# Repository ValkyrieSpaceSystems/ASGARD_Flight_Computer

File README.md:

# Asgard Flight Computer

An open-source high power rocketry flight computer designed for long-term affordability through flexibility, modularity, and expandability. Designed to fly with [ODIN flight software](https://github.com/ValkyrieSpaceSystems/ODIN_Flight_Software) and communicate with the [Midgard ground station](https://github.com/ValkyrieSpaceSystems/MIDGARD_Ground_Control) over the [BIFROST protocol](https://github.com/ValkyrieSpaceSystems/BIFROST_Communications_Protocol).

---

## Sensors

| Component | Part | Interface |
|---|---|---|
| Low-altitude barometer | BMP581 | SPI |
| High-altitude barometer *(optional)* | MS5607 | SPI |
| Low-g IMU | BMI270 | SPI |
| Mid-g IMU | BMI088 | SPI |
| High-g accelerometer | H3LIS331DLTR | SPI |
| Magnetometer | MMC5983MA | SPI |
| GNSS | MAX-M10S | UART |
| Current monitor | INA226 | I2C |

---

## Pyrotechnics

3 independent events, 2 channels each (6 total). High-side arming via external switch keeps all channels unpowered until deliberately armed. Each channel has its own independent low-side MOSFET.

---

## Servo Control

6 outputs — a 4-channel group for fin deflection and a 2-channel group for thrust vector control. Each group is independently configurable via jumper to run from battery or regulated 5V.

---

## Communications

Interface agnostic — any physical transport (XBee, ELRS, RS-485, Bluetooth, CAN, USB, etc.) can carry BIFROST traffic with no firmware changes. A bypass switch port enables autonomous operation if ground station comms are unavailable.

---

## Expansion

2× SPI, 3× UART, 2× I2C, 1× CAN expansion ports, plus 2 GPIO breakout pins. Pyro arm and servo arm signals are also broken out for auxiliary boards.

**Current expansion boards:** RS-485, GPIO breakout

**Planned:** camera module, extra sensors, payload, multi-stage, Bluetooth/WiFi, high-power servos, pyro expansion

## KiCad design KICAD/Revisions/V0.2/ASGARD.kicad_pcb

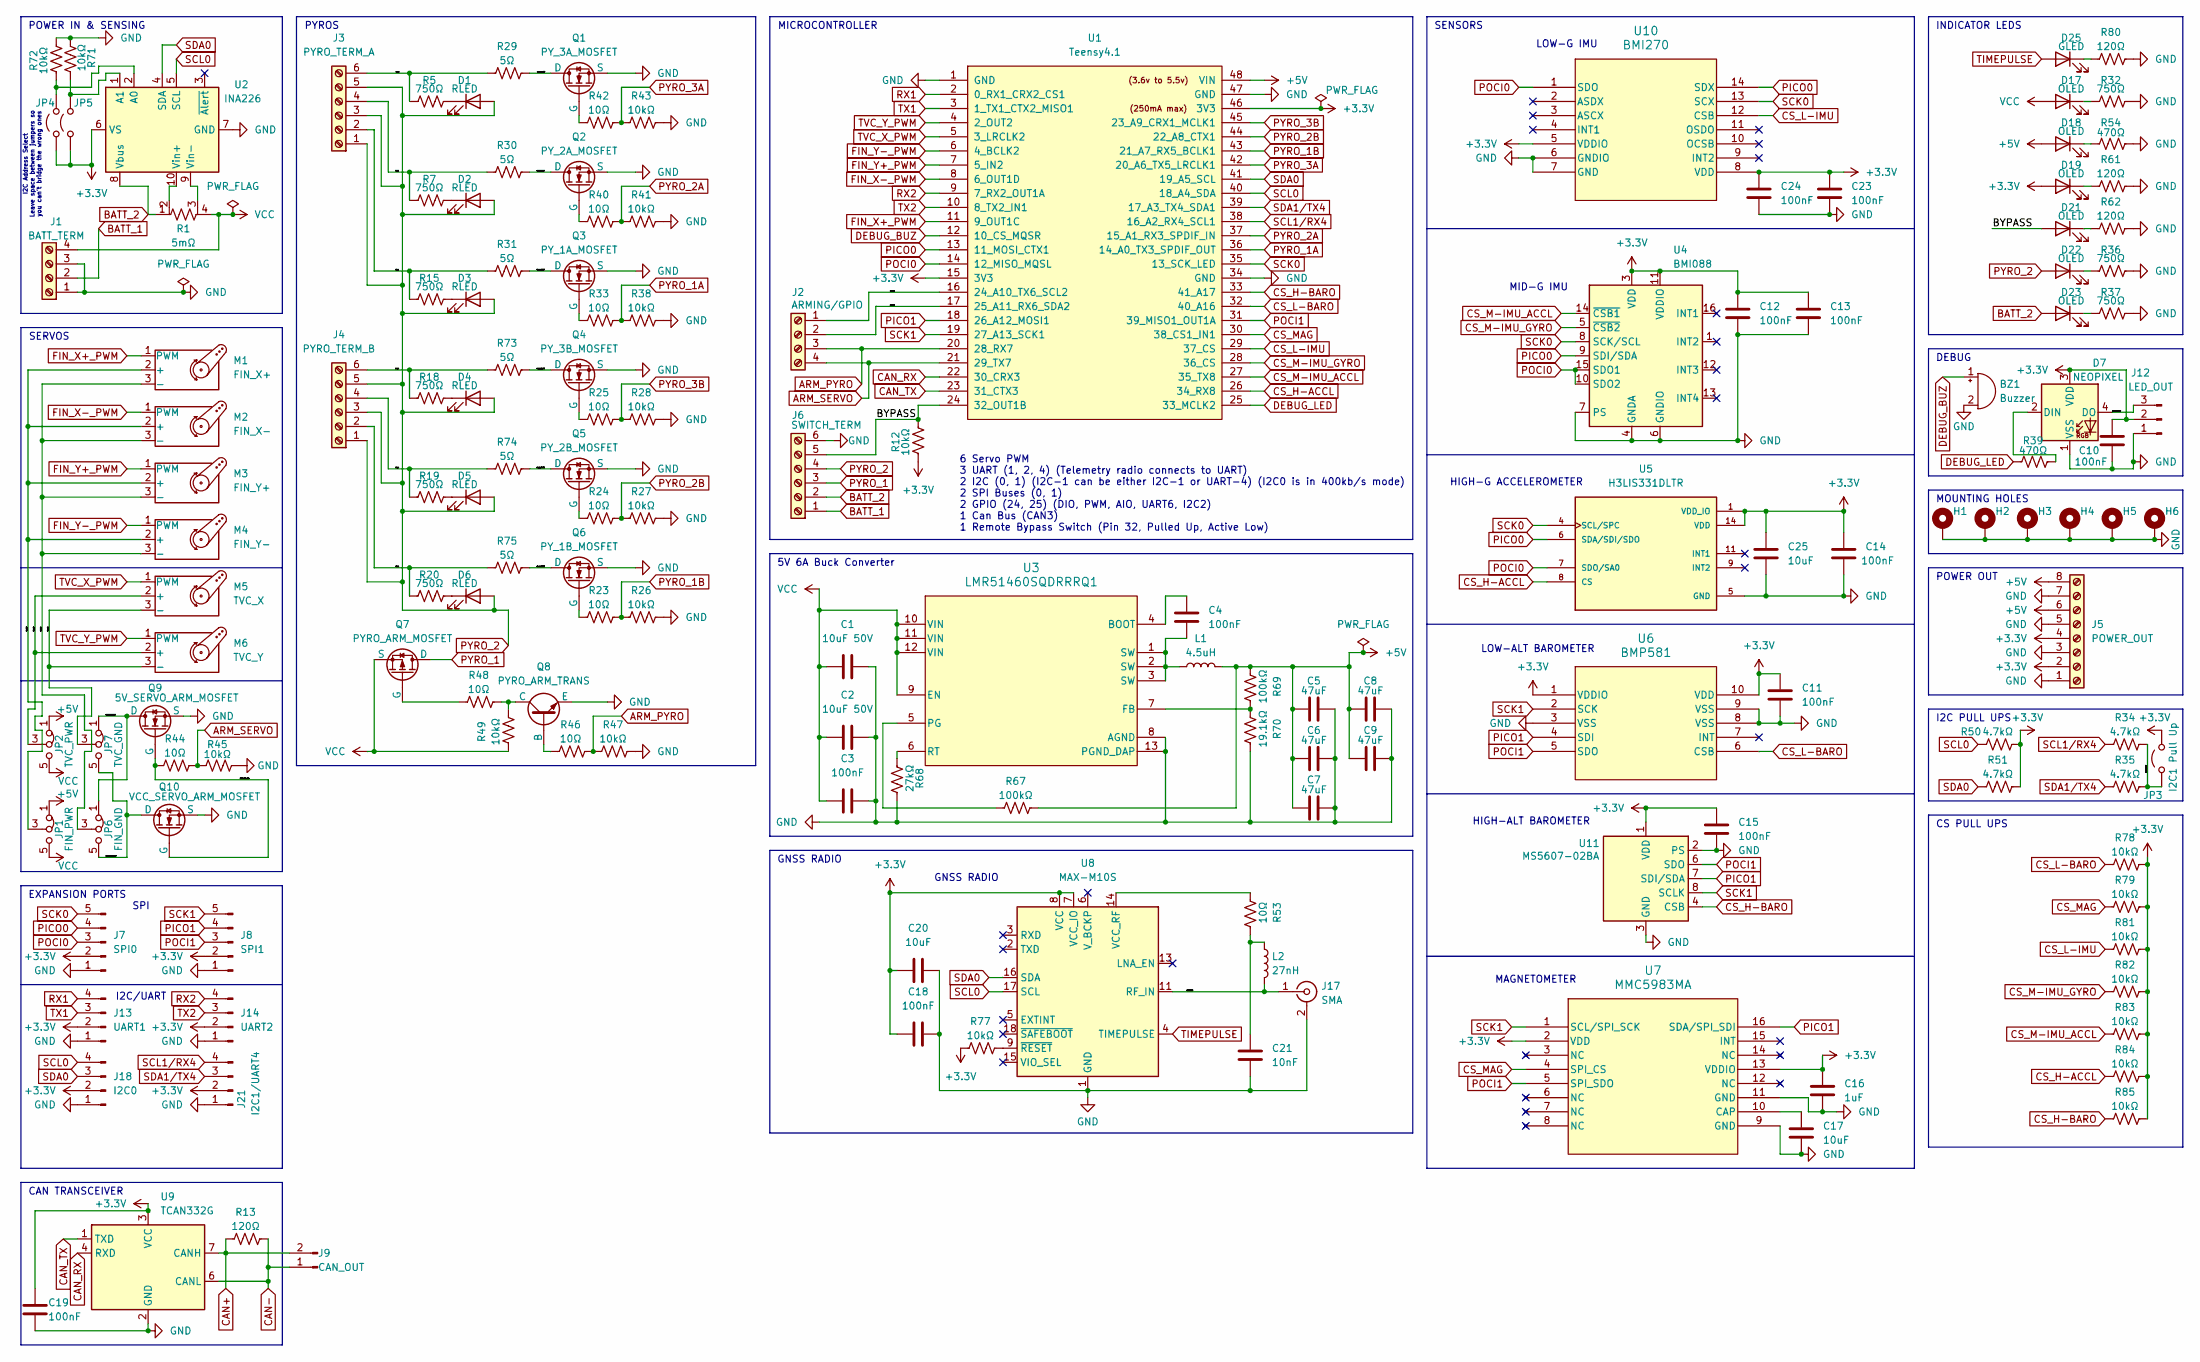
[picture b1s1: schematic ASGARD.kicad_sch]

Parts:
BZ1: Buzzer; Buzzer_CUI_CPT-9019S-SMT
C1, C2: 10uF 50V; C_1210_3225Metric
C3, C4, C10, C11, C12, C13, C14, C15, C18, C19, C23, C24: 100nF; C_0603_1608Metric
C5, C6, C7, C8, C9: 47uF; C_1210_3225Metric
C16: 1uF; C_0603_1608Metric
C17, C20, C25: 10uF; C_0603_1608Metric
C21: 10nF; C_0603_1608Metric
D1, D2, D3, D4, D5, D6: RLED; LED_0603_1608Metric
D7: NEOPIXEL; LED_Inolux_IN-PI554FCH_PLCC4_5.0x5.0mm_P3.2mm
D17, D18, D19, D21, D22, D23: OLED; LED_0603_1608Metric
D25: GLED; LED_0603_1608Metric
H1, H2, H3, H4, H5, H6: MountingHole_Pad; MountingHole_2.5mm_Pad
J1: BATT_TERM; TerminalBlock_4Ucon_1x04_P3.50mm_Horizontal
J2: ARMING/GPIO; TerminalBlock_4Ucon_1x04_P3.50mm_Horizontal
J3: PYRO_TERM_A; TerminalBlock_4Ucon_1x06_P3.50mm_Horizontal
J4: PYRO_TERM_B; TerminalBlock_4Ucon_1x06_P3.50mm_Horizontal
J5: POWER_OUT; TerminalBlock_4Ucon_1x08_P3.50mm_Horizontal
J6: SWITCH_TERM; TerminalBlock_4Ucon_1x06_P3.50mm_Horizontal
J7: SPI0; JST_SH_BM05B-SRSS-TB_1x05-1MP_P1.00mm_Vertical
J8: SPI1; JST_SH_BM05B-SRSS-TB_1x05-1MP_P1.00mm_Vertical
J9: CAN_OUT; JST_SH_BM02B-SRSS-TB_1x02-1MP_P1.00mm_Vertical
J12: LED_OUT; JST_SH_BM03B-SRSS-TB_1x03-1MP_P1.00mm_Vertical
J13: UART1; JST_SH_BM04B-SRSS-TB_1x04-1MP_P1.00mm_Vertical
J14: UART2; JST_SH_BM04B-SRSS-TB_1x04-1MP_P1.00mm_Vertical
J17: SMA; SMA_Amphenol_132134-11_Vertical
J18: I2C0; JST_SH_BM04B-SRSS-TB_1x04-1MP_P1.00mm_Vertical
J21: I2C1/UART4; JST_SH_BM04B-SRSS-TB_1x04-1MP_P1.00mm_Vertical
JP1: FIN_PWR; PinHeader_2x03_P2.54mm_Vertical
JP2: TVC_PWR; PinHeader_2x03_P2.54mm_Vertical
JP3: I2C1 Pull Up; PinHeader_1x02_P2.54mm_Vertical
JP4, JP5: Jumper_2_Open; PinHeader_1x02_P2.54mm_Vertical
JP6: FIN_GND; PinHeader_2x03_P2.54mm_Vertical
JP7: TVC_GND; PinHeader_2x03_P2.54mm_Vertical
L1: 4.5uH; IND_SRR1208-120ML
L2: 27nH; L_0402_1005Metric
M1: FIN_X+; PinHeader_1x03_P2.54mm_Vertical
M2: FIN_X-; PinHeader_1x03_P2.54mm_Vertical
M3: FIN_Y+; PinHeader_1x03_P2.54mm_Vertical
M4: FIN_Y-; PinHeader_1x03_P2.54mm_Vertical
M5: TVC_X; PinHeader_1x03_P2.54mm_Vertical
M6: TVC_Y; PinHeader_1x03_P2.54mm_Vertical
Q1: PY_3A_MOSFET; SOT-23-3
Q2: PY_2A_MOSFET; SOT-23-3
Q3: PY_1A_MOSFET; SOT-23-3
Q4: PY_3B_MOSFET; SOT-23-3
Q5: PY_2B_MOSFET; SOT-23-3
Q6: PY_1B_MOSFET; SOT-23-3
Q7: PYRO_ARM_MOSFET; SOT-23-6_Handsoldering
Q8: PYRO_ARM_TRANS; SOT-23-3
Q9: 5V_SERVO_ARM_MOSFET; Infineon_PG-TDSON-8_6.15x5.15mm
Q10: VCC_SERVO_ARM_MOSFET; Infineon_PG-TDSON-8_6.15x5.15mm
R1: 5mΩ; RES_WSLP2726L2000FEA
R5, R7, R15, R18, R19, R20, R32, R36, R37: 750Ω; R_0805_2012Metric
R12, R26, R27, R28, R38, R41, R43, R45, R47, R49, R71, R72, R77, R78, R79, R81, R82, R83, R84, R85: 10kΩ; R_0805_2012Metric
R13, R61, R62, R80: 120Ω; R_0805_2012Metric
R23, R24, R25, R33, R40, R42, R44, R46, R48, R53: 10Ω; R_0805_2012Metric
R29, R30, R31, R73, R74, R75: 5Ω; R_0805_2012Metric
R34, R35, R50, R51: 4.7kΩ; R_0805_2012Metric
R39, R54: 470Ω; R_0805_2012Metric
R67, R69: 100kΩ; R_0805_2012Metric
R68: 27kΩ; R_0805_2012Metric
R70: 19.1kΩ; R_0805_2012Metric
U1: Teensy4.1; Teensy41
U2: INA226; TSSOP-10_3x3mm_P0.5mm
U3: LMR51460SQDRRRQ1; DRR0012E-IPC_A
U4: BMI088; Bosch_LGA-16_4.5x3mm_P0.5mm_LayoutBorder7x1y_ClockwisePinNu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
U5: H3LIS331DLTR; QFN300X300X100-16N
U6: BMP581; QFN10_BMP581_BOS
U7: MMC5983MA; MMC5983MA_MEM
U8: MAX-M10S; ublox_MAX
U9: TCAN332G; TSOT-23-8_HandSoldering
U10: BMI270; BMI270_BOS
U11: MS5607-02BA; LGA-8_3x5mm_P1.25mm

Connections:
+3.3V: C10.2, C11.2, C12.1, C13.2, C14.2, C15.2, C16.1, C18.2, C19.1, C20.1, C23.1, C24.2, C25.1, D7.3 (VDD), D19.2 (A), J5.2, J5.4, J7.2, J8.2, J12.2, J13.2, J14.2, J18.2, J21.2, JP3.2 (B), JP4.1 (A), JP5.1 (A), R12.1, R50.2, R51.2, R77.1, R78.2, R79.2, R81.2, R82.2, R83.2, R84.2, R85.2, U1.15 (3V3), U1.46 (3V3), U2.6 (VS), U4.3 (VDD), U4.11 (VDDIO), U5.1 (VDD_IO), U5.14 (VDD), U5.15 (VDD), U6.1 (VDDIO), U6.10 (VDD), U7.2 (VDD), U7.13 (VDDIO), U8.7 (VCC_IO), U8.8 (VCC), U9.3 (VCC), U10.5 (VDDIO), U10.8 (VDD), U11.1 (VDD)
+5V: C5.2, C6.2, C7.2, C8.2, C9.2, D18.2 (A), J5.6, J5.8, JP1.1 (A), JP2.1 (A), L1.2, R67.2, R69.1, U1.48 (VIN)
/5V_SERVO_MOSFET: JP6.1 (A), JP7.1 (A), Q9.5 (D)
/BYPASS: D21.2 (A), J6.5, R12.2, U1.24 (32_OUT1B)
/DEBUG_LED_OUT: D7.4 (DO), J12.3
/FIN_GND: JP6.3 (C), M1.3 (-), M2.3 (-), M3.3 (-), M4.3 (-)
/FIN_PWR: JP1.3 (C), M1.2 (+), M2.2 (+), M3.2 (+), M4.2 (+)
/GPIO_24: J2.1, U1.16 (24_A10_TX6_SCL2)
/GPIO_25: J2.2, U1.17 (25_A11_RX6_SDA2)
/I2C1_PULL_UP: JP3.1 (A), R34.2, R35.2
/MICROSTRIP: J17.1 (In), L2.2, U8.11 (RF_IN)
/PY_1A: J3.2, R15.1, R31.1
/PY_1A_MOSFET: Q3.3 (D), R31.2
/PY_1B: J4.2, R20.1, R75.1
/PY_1B_MOSFET: Q6.3 (D), R75.2
/PY_2A: J3.4, R7.1, R30.1
/PY_2A_MOSFET: Q2.3 (D), R30.2
/PY_2B: J4.4, R19.1, R74.1
/PY_2B_MOSFET: Q5.3 (D), R74.2
/PY_3A: J3.6, R5.1, R29.1
/PY_3A_MOSFET: Q1.3 (D), R29.2
/PY_3B: J4.6, R18.1, R73.1
/PY_3B_MOSFET: Q4.3 (D), R73.2
/SERVO_ARM_GATE: Q9.4 (G), Q10.4 (G), R44.1
/TVC_GND: JP7.3 (C), M5.3 (-), M6.3 (-)
/TVC_PWR: JP2.3 (C), M5.2 (+), M6.2 (+)
/VCC_SERVO_MOSFET: JP6.5 (B), JP7.5 (B), Q10.5 (D)
ARM_PYRO: J2.3, R46.2, R47.1, U1.20 (28_RX7)
ARM_SERVO: J2.4, R44.2, R45.1, U1.21 (29_TX7)
BATT_1: J1.2, J6.1
BATT_2: D23.2 (A), J6.2, R1.1, U2.8 (Vbus)
CAN+: J9.2, R13.1, U9.7 (CANH)
CAN-: J9.1, R13.2, U9.6 (CANL)
CAN_RX: U1.22 (30_CRX3), U9.4 (RXD)
CAN_TX: U1.23 (31_CTX3), U9.1 (TXD)
CS_H-ACCL: R84.1, U1.26 (34_RX8), U5.8 (CS)
CS_H-BARO: R85.1, U1.33 (41_A17), U11.4 (CSB), U11.5 (CSB)
CS_L-BARO: R78.1, U1.32 (40_A16), U6.6 (CSB)
CS_L-IMU: R81.1, U1.29 (37_CS), U10.12 (CSB)
CS_M-IMU_ACCL: R83.1, U1.27 (35_TX8), U4.14 (~CSB1)
CS_M-IMU_GYRO: R82.1, U1.28 (36_CS), U4.5 (~CSB2)
CS_MAG: R79.1, U1.30 (38_CS1_IN1), U7.4 (SPI_CS)
DEBUG_BUZ: BZ1.1 (+), U1.12 (10_CS_MQSR)
DEBUG_LED: R39.1, U1.25 (33_MCLK2)
FIN_X+_PWM: M1.1 (PWM), U1.11 (9_OUT1C)
FIN_X-_PWM: M2.1 (PWM), U1.8 (6_OUT1D)
FIN_Y+_PWM: M3.1 (PWM), U1.7 (5_IN2)
FIN_Y-_PWM: M4.1 (PWM), U1.6 (4_BCLK2)
GND: BZ1.2 (-), C1.2, C2.2, C3.2, C5.1, C6.1, C7.1, C8.1, C9.1, C10.1, C11.1, C12.2, C13.1, C14.1, C15.1, C16.2, C17.2, C18.1, C19.2, C20.2, C21.2, C23.2, C24.1, C25.2, D7.1 (VSS), H1.1 (1_1), H2.1 (1_1), H3.1 (1_1), H4.1 (1_1), H5.1 (1_1), H6.1 (1_1), J1.1, J1.3, J5.1, J5.3, J5.5, J5.7, J6.6, J7.1, J8.1, J12.1, J13.1, J14.1, J17.2 (Ext), J18.1, J21.1, Q1.2 (S), Q2.2 (S), Q3.2 (S), Q4.2 (S), Q5.2 (S), Q6.2 (S), Q8.2 (E), Q9.1 (S), Q10.1 (S), R26.2, R27.2, R28.2, R32.2, R36.2, R37.2, R38.2, R41.2, R43.2, R45.2, R47.2, R54.2, R61.2, R62.2, R68.2, R70.2, R71.1, R72.2, R80.2, U1.1 (GND), U1.34 (GND), U1.47 (GND), U2.7 (GND), U3.8 (AGND), U3.13 (PGND_DAP), U4.2 (GNDA), U4.4 (GNDA), U4.6 (GNDIO), U4.7 (PS), U5.5 (GND), U5.10 (GND), U5.12 (GND), U5.13 (GND), U5.16 (GND), U6.3 (VSS), U6.8 (VSS), U6.9 (VSS), U7.9 (GND), U7.11 (GND), U8.1 (GND), U8.10 (GND), U8.12 (GND), U9.2 (GND), U10.6 (GNDIO), U10.7 (GND), U11.2 (PS), U11.3 (GND)
unnamed: C4.2, L1.1, U3.1 (SW), U3.2 (SW), U3.3 (SW)
unnamed: C21.1, L2.1, R53.2
unnamed: D1.1 (K), R5.2
unnamed: D2.1 (K), R7.2
unnamed: D3.1 (K), R15.2
unnamed: D4.1 (K), R18.2
unnamed: D5.1 (K), R19.2
unnamed: D6.1 (K), R20.2
unnamed: D7.2 (DIN), R39.2
unnamed: D17.1 (K), R32.1
unnamed: D18.1 (K), R54.1
unnamed: D19.1 (K), R61.1
unnamed: D21.1 (K), R62.1
unnamed: D22.1 (K), R36.1
unnamed: D23.1 (K), R37.1
unnamed: D25.1 (K), R80.1
unnamed: JP4.2 (B), R72.1, U2.2 (A0)
unnamed: JP5.2 (B), R71.2, U2.1 (A1)
unnamed: Q1.1 (G), R42.1
unnamed: Q2.1 (G), R40.1
unnamed: Q3.1 (G), R33.1
unnamed: Q4.1 (G), R25.1
unnamed: Q5.1 (G), R24.1
unnamed: Q6.1 (G), R23.1
unnamed: Q7.3 (G), R48.1
unnamed: Q8.1 (B), R46.1
unnamed: Q8.3 (C), R48.2, R49.2
unnamed: R1.2, U2.10 (Vin+)
unnamed: R1.3, U2.9 (Vin-)
unnamed: C4.1, U3.4 (BOOT)
unnamed: R69.2, R70.1, U3.7 (FB)
unnamed: R67.1, U3.5 (PG)
unnamed: R68.1, U3.6 (RT)
unnamed: C17.1, U7.10 (CAP)
unnamed: R53.1, U8.14 (VCC_RF)
unnamed: R77.2, U8.9 (~RESET)
PICO0: J7.4, U1.13 (11_MOSI_CTX1), U4.9 (SDI/SDA), U5.6 (SDA/SDI/SDO), U10.14 (SDX)
PICO1: J8.4, U1.18 (26_A12_MOSI1), U6.4 (SDI), U7.16 (SDA/SPI_SDI), U11.7 (SDI/SDA)
POCI0: J7.3, U1.14 (12_MISO_MQSL), U4.10 (SDO2), U4.15 (SDO1), U5.7 (SDO/SA0), U10.1 (SDO)
POCI1: J8.3, U1.31 (39_MISO1_OUT1A), U6.5 (SDO), U7.5 (SPI_SDO), U11.6 (SDO)
PYRO_1: J6.3, Q7.1 (D)
PYRO_1A: R33.2, R38.1, U1.36 (14_A0_TX3_SPDIF_OUT)
PYRO_1B: R23.2, R26.1, U1.43 (21_A7_RX5_BCLK1)
PYRO_2: D1.2 (A), D2.2 (A), D3.2 (A), D4.2 (A), D5.2 (A), D6.2 (A), D22.2 (A), J3.1, J3.3, J3.5, J4.1, J4.3, J4.5, J6.4
PYRO_2A: R40.2, R41.1, U1.37 (15_A1_RX3_SPDIF_IN)
PYRO_2B: R24.2, R27.1, U1.44 (22_A8_CTX1)
PYRO_3A: R42.2, R43.1, U1.42 (20_A6_TX5_LRCLK1)
PYRO_3B: R25.2, R28.1, U1.45 (23_A9_CRX1_MCLK1)
RX1: J13.4, U1.2 (0_RX1_CRX2_CS1)
RX2: J14.4, U1.9 (7_RX2_OUT1A)
SCK0: J7.5, U1.35 (13_SCK_LED), U4.8 (SCK/SCL), U5.4 (SCL/SPC), U10.13 (SCX)
SCK1: J8.5, U1.19 (27_A13_SCK1), U6.2 (SCK), U7.1 (SCL/SPI_SCK), U11.8 (SCLK)
SCL0: J18.4, R50.1, U1.40 (18_A4_SDA), U2.5 (SCL), U8.17 (SCL)
SCL1/RX4: J21.4, R34.1, U1.38 (16_A2_RX4_SCL1)
SDA0: J18.3, R51.1, U1.41 (19_A5_SCL), U2.4 (SDA), U8.16 (SDA)
SDA1/TX4: J21.3, R35.1, U1.39 (17_A3_TX4_SDA1)
TIMEPULSE: D25.2 (A), U8.4 (TIMEPULSE)
TVC_X_PWM: M5.1 (PWM), U1.5 (3_LRCLK2)
TVC_Y_PWM: M6.1 (PWM), U1.4 (2_OUT2)
TX1: J13.3, U1.3 (1_TX1_CTX2_MISO1)
TX2: J14.3, U1.10 (8_TX2_IN1)
VCC: C1.1, C2.1, C3.1, D17.2 (A), J1.4, JP1.5 (B), JP2.5 (B), Q7.4 (S), R1.4, R49.1, U3.9 (EN), U3.10 (VIN), U3.11 (VIN), U3.12 (VIN)

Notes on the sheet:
MICROCONTROLLER
5V 6A Buck Converter
CS PULL UPS
HIGH-G ACCELEROMETER
MAGNETOMETER
DEBUG
I2C Address Select Leave space between jumpers so you can't bridge the wrong ones
I2C/UART
SERVOS
LOW-G IMU
INDICATOR LEDS
I2C PULL UPS
MOUNTING HOLES
POWER IN & SENSING
SENSORS
PYROS
GNSS RADIO
HIGH-ALT BAROMETER
6 Servo PWM 3 UART (1, 2, 4) (Telemetry radio connects to UART) 2 I2C (0, 1) (I2C-1 can be either I2C-1 or UART-4) (I2C0 is in 400kb/s mode) 2 SPI Buses (0, 1) 2 GPIO (24, 25) (DIO, PWM, AIO, UART6, I2C2) 1 Can Bus (CAN3) 1 Remote Bypass Switch (Pin 32, Pulled Up, Active Low)
POWER OUT
SPI
EXPANSION PORTS
LOW-ALT BAROMETER
MID-G IMU
CAN TRANSCEIVER

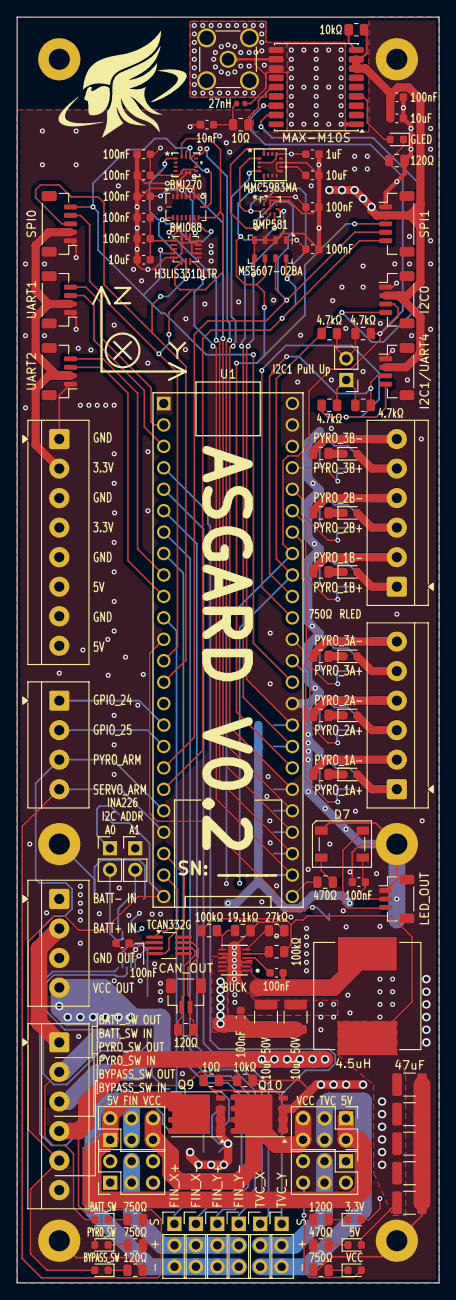
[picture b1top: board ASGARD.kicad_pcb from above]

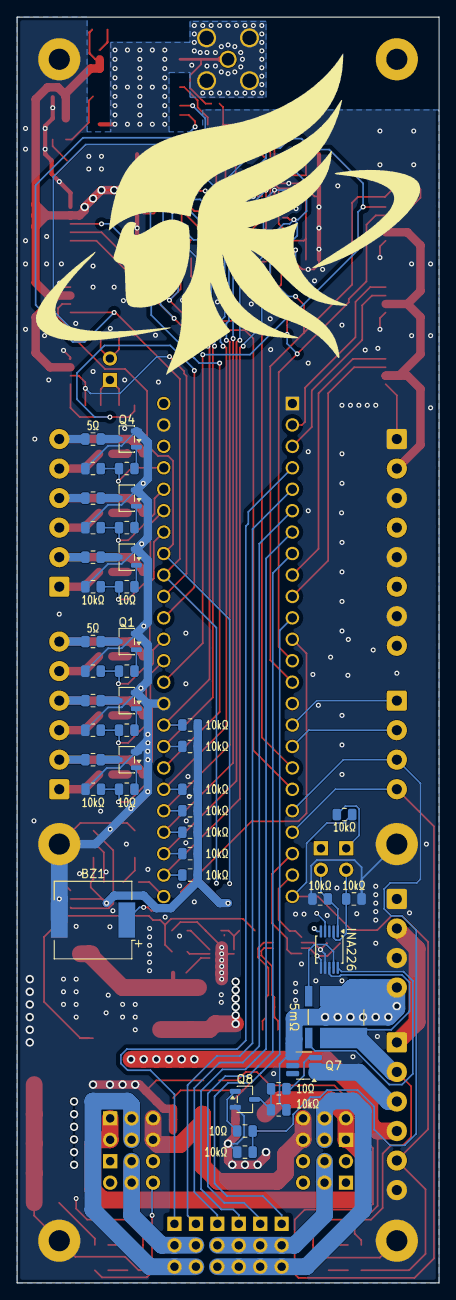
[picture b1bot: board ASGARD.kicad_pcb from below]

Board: 4 copper layers, 50.0 x 150.0 mm, 156 parts (43 on the bottom side), 111 nets.

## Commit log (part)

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2026-06-08 made ProjectIO Project
